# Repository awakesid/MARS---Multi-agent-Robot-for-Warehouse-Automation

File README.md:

# M.A.R.S — Multi Agent Robot System for Warehouse Automation

Modular multi-robot warehouse automation system using sensor fusion (encoders + overhead camera/ArUco) for localization, with ROS 2 based central coordination and ESP32-based robot firmware.

## Overview

- Differential-drive robots with ESP32 microcontrollers, encoder-based odometry, and servo grippers
- Overhead camera + ArUco markers for global pose estimation of robots, loads, and dropzones
- ROS 2 central controller handles task allocation, path planning, collision avoidance
- Robot ↔ central controller communication over UDP (JSON commands)
- Supports single/multi-robot operation, priority-based and thread-based task execution, single/double dropzone configurations

## System Architecture

```
Overhead Camera → aruco_detector (OpenCV) → /bot_poses, /loads, /dropzone
                                                      ↓
                                              task_manager (ROS 2)
                                        (task allocation, collision avoidance, navigation)
                                                      ↓
                                          UDP (JSON) ↔ ESP32 robots
```

## Hardware

- ESP32-WROOM / ESP32-S3
- N20 DC motors with encoders
- L293D dual H-bridge motor driver
- Servo gripper
- Li-Po battery
- Custom double-sided PCB (KiCad design, in-house etched)
- 3D printed chassis (Fusion 360 + Bambu Lab printer)

## Software Stack

- **Firmware**: C++ (Arduino/ESP32), non-blocking UDP + Telnet handlers, PID for straight-line motion
- **Central Controller**: ROS 2 (Python/C++), OpenCV for ArUco detection
- **Communication**: ROS 2 topics (internal), UDP/WiFi (robot control)

## Repository Structure

```
/firmware        # ESP32 robot firmware (motor control, encoder PID, UDP command handling)
/ros2_ws          # ROS 2 packages: camera_node, aruco_detector, task_manager
/pcb              # KiCad PCB design files
/cad              # Fusion 360 chassis design files
/docs             # Report, diagrams, results
```

## Firmware Command Protocol

Robots listen on a dedicated UDP port for JSON commands:

```json
{"id": 1, "cmd": "FORWARD", "dist": 200}
{"id": 1, "cmd": "TURN_L", "angle": 90}
{"id": 1, "cmd": "GRAB"}
```

Supported commands: `FORWARD`, `BACKWARD`, `TURN_L`, `TURN_R`, `GRAB`, `RELEASE`, `STOP`
Each command receives an `ack` on receipt and a `done` reply on completion. Odometry is broadcast at 10 Hz.

## Setup

### Firmware
1. Open `/firmware` in Arduino IDE / PlatformIO
2. Set `BOT_ID`, WiFi credentials, and target UDP port per robot
3. Flash to ESP32

### Central Controller
1. Requires ROS 2 (tested on Humble/Iron), OpenCV, `opencv-contrib` (ArUco module)
2. Build workspace:
   ```
   cd ros2_ws
   colcon build
   source install/setup.bash
   ```
3. Launch nodes:
   ```
   ros2 launch mars_bringup mars.launch.py
   ```

Thread-based multi-robot execution with double dropzone gave the best throughput; single dropzone increases collision risk and coordination overhead.

## Team
- Amrit Kumar Banjade
- Laxmi Prasad Upadhyaya
- Siddartha Gupta
- Sumit Sigdel

Department of Electronics and Computer Engineering, Pashchimanchal Campus, IOE, Tribhuvan University
Supervisor: Asst. Prof. Er. Hom Nath Tiwari

For a more detailed description, you can refer `MARS_report.pdf`

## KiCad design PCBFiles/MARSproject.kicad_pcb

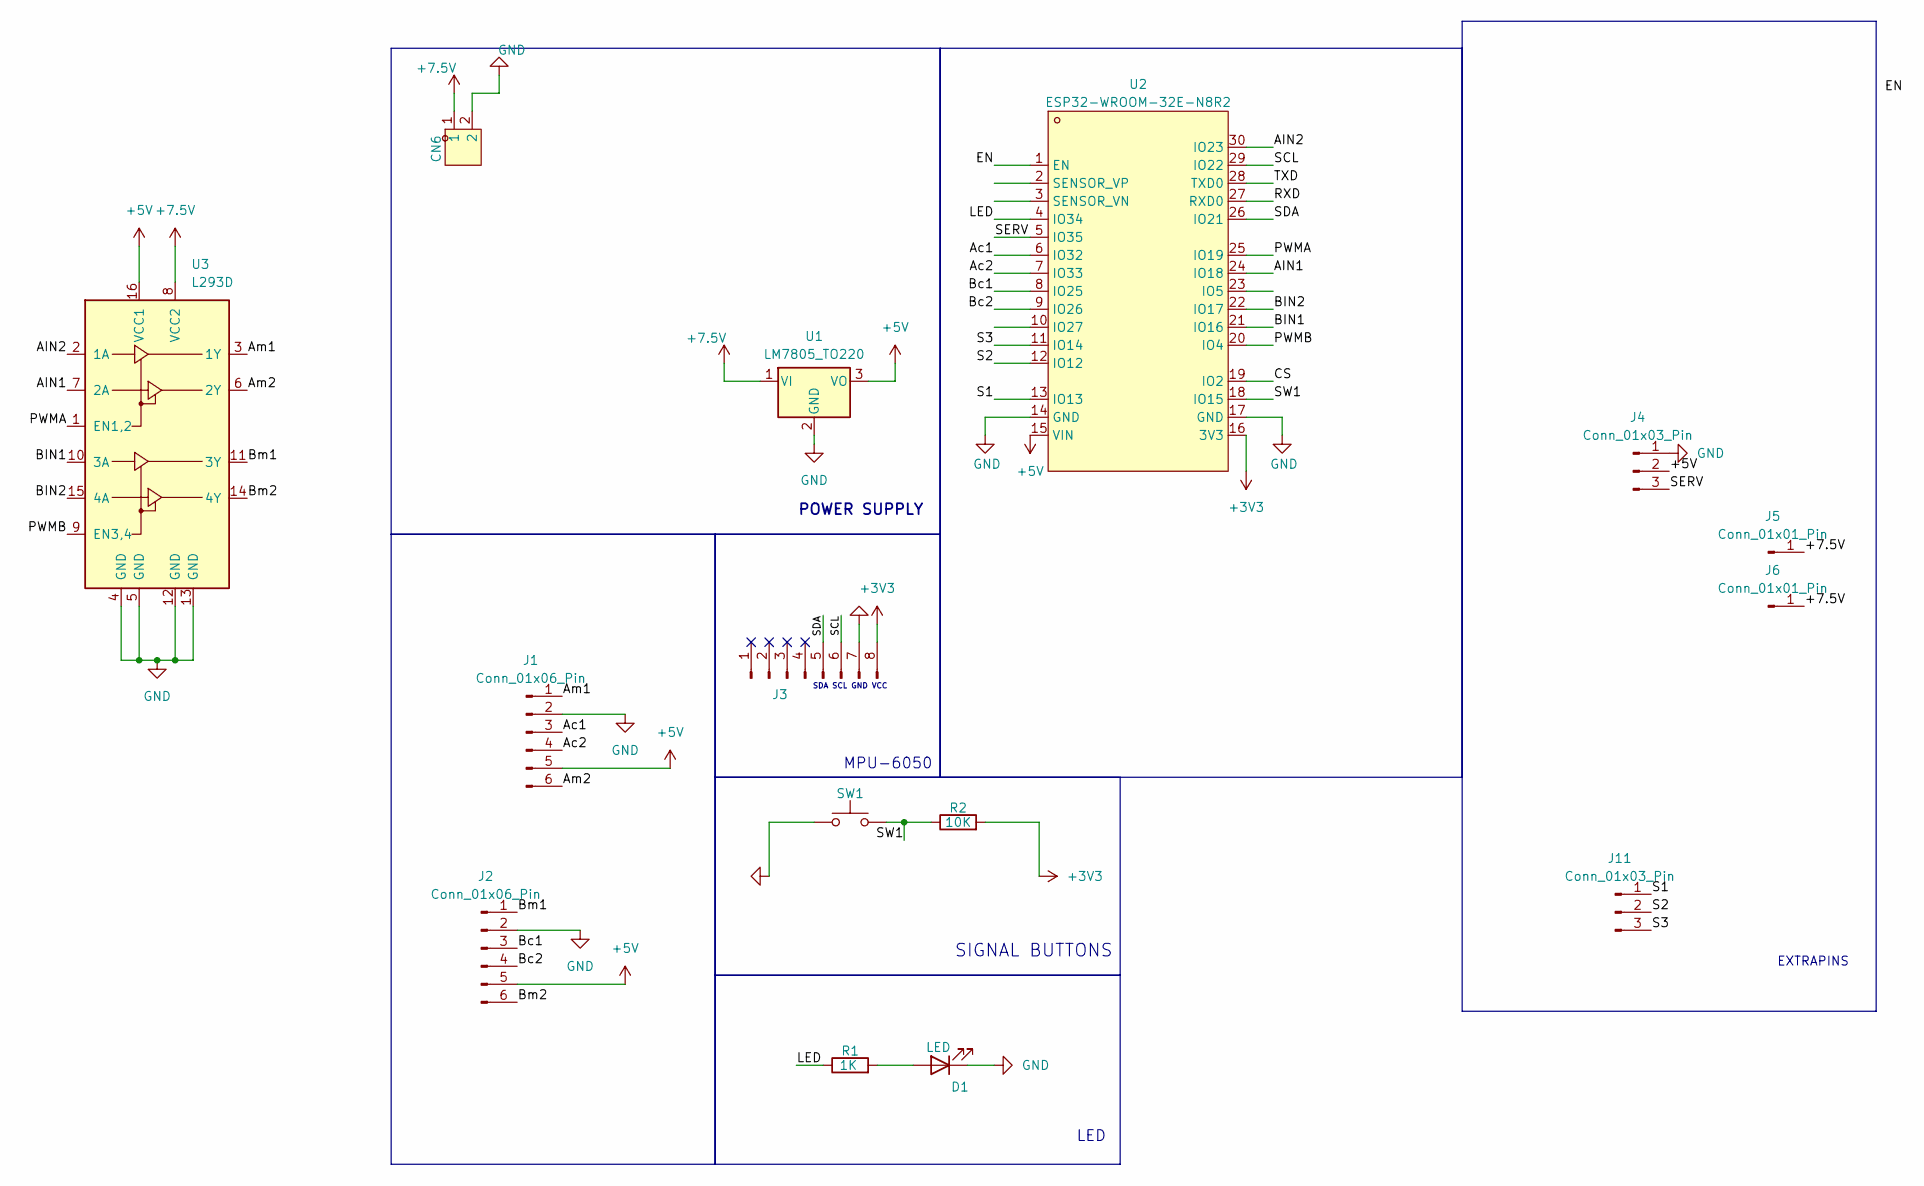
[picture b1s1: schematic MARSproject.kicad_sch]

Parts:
CN6: B2B-XH-A (LF)(SN); CONN-TH_B2B-XH-A-LF-SN; LCSC Part C158012
D1: LED; LED_D1.8mm_W3.3mm_H2.4mm
J1, J2: Conn_01x06_Pin; PinHeader_1x06_P2.54mm_Vertical
J3: Conn_01x08_Pin; PinHeader_1x08_P2.54mm_Vertical
J4, J11: Conn_01x03_Pin; PinHeader_1x03_P2.54mm_Vertical
J5, J6: Conn_01x01_Pin; PinHeader_1x01_P2.54mm_Vertical
R1: 1K; R_Axial_DIN0204_L3.6mm_D1.6mm_P2.54mm_Vertical
R2: 10K; R_Axial_DIN0204_L3.6mm_D1.6mm_P2.54mm_Vertical
SW1: SW_Push; SW_PUSH_6mm_H4.3mm
U1: LM7805_TO220; TO-220-3_Vertical
U2: ESP32-WROOM-32E-N8R2; esp32 dev board; LCSC Part C5361945
U3: L293D; DIP-16_W7.62mm

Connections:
+3V3: J3.8, R2.2, U2.16 (3V3)
+5V: J1.5, J2.5, J4.2, U1.3 (VO), U2.15 (VIN), U3.16 (VCC1)
+7.5V: CN6.1, J5.1, J6.1, U1.1 (VI), U3.8 (VCC2)
/AIN1: U2.24 (IO18), U3.7 (2A)
/AIN2: U2.30 (IO23), U3.2 (1A)
/Ac1: J1.3, U2.6 (IO32)
/Ac2: J1.4, U2.7 (IO33)
/Am1: J1.1, U3.3 (1Y)
/Am2: J1.6, U3.6 (2Y)
/BIN1: U2.21 (IO16), U3.10 (3A)
/BIN2: U2.22 (IO17), U3.15 (4A)
/Bc1: J2.3, U2.8 (IO25)
/Bc2: J2.4, U2.9 (IO26)
/Bm1: J2.1, U3.11 (3Y)
/Bm2: J2.6, U3.14 (4Y)
/CS: U2.19 (IO2)
/EN: U2.1 (EN)
/LED: R1.1, U2.4 (IO34)
/PWMA: U2.25 (IO19), U3.1 (EN1,2)
/PWMB: U2.20 (IO4), U3.9 (EN3,4)
/RXD: U2.27 (RXD0)
/S1: J11.1, U2.13 (IO13)
/S2: J11.2, U2.12 (IO12)
/S3: J11.3, U2.11 (IO14)
/SCL: J3.6, U2.29 (IO22)
/SDA: J3.5, U2.26 (IO21)
/SERV: J4.3, U2.5 (IO35)
/SW1: R2.1, SW1.2, U2.18 (IO15)
/TXD: U2.28 (TXD0)
GND: CN6.2, D1.1 (K), J1.2, J2.2, J3.7, J4.1, SW1.1, U1.2 (GND), U2.14 (GND), U2.17 (GND), U3.4 (GND), U3.5 (GND), U3.12 (GND), U3.13 (GND)
unnamed: D1.2 (A), R1.2

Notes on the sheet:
SDA SCL GND VCC
SIGNAL BUTTONS
MPU-6050
POWER SUPPLY
EXTRAPINS
LED

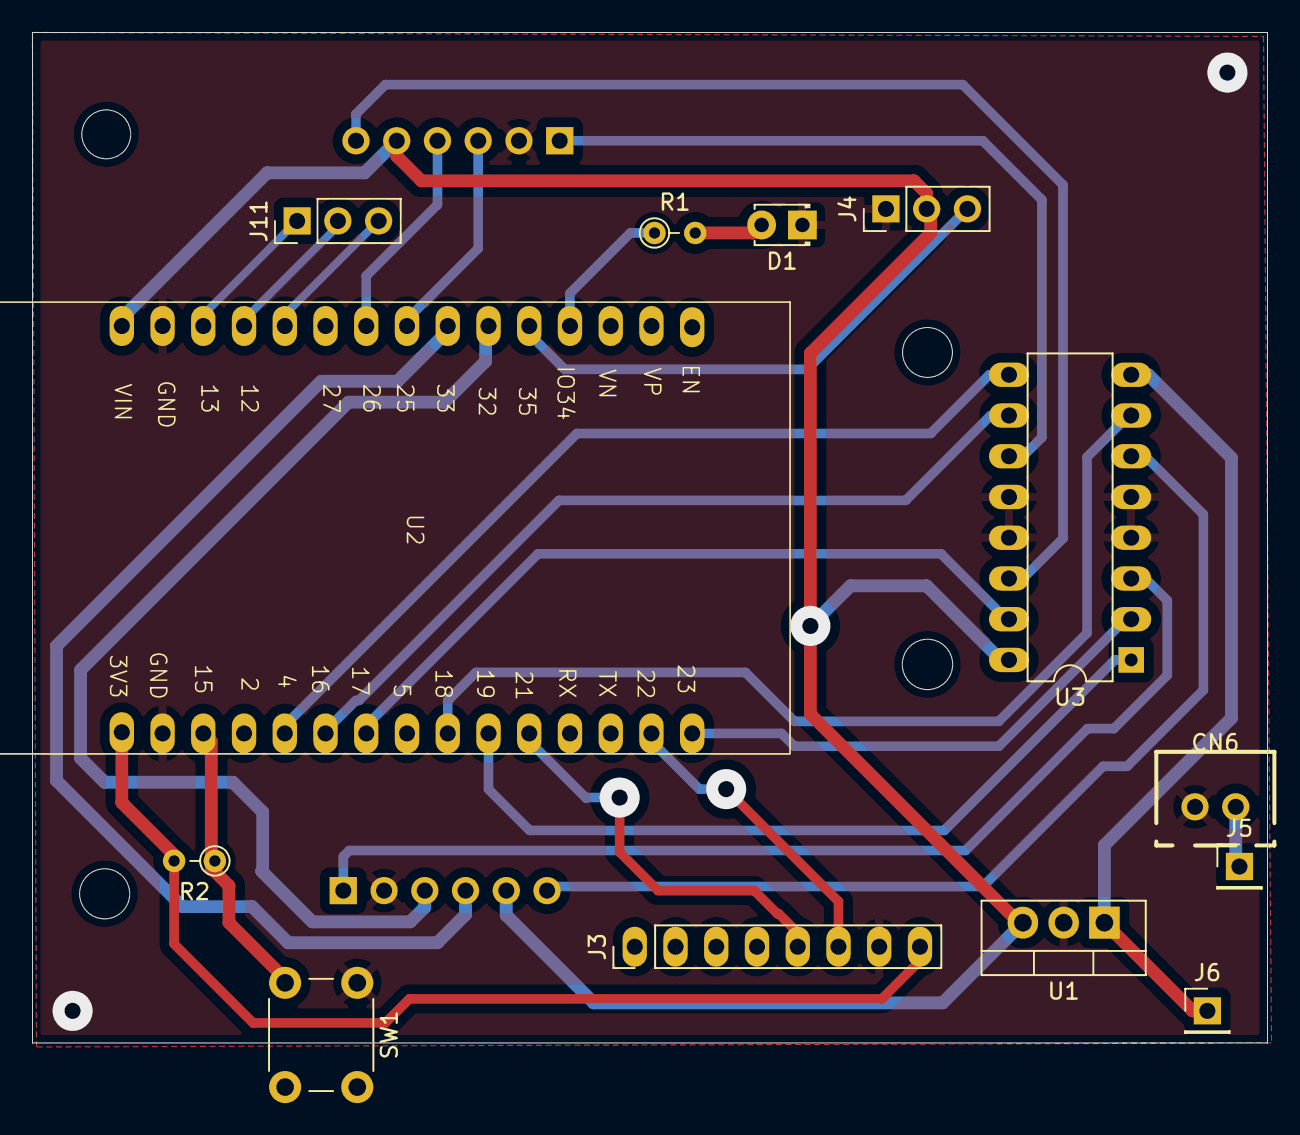
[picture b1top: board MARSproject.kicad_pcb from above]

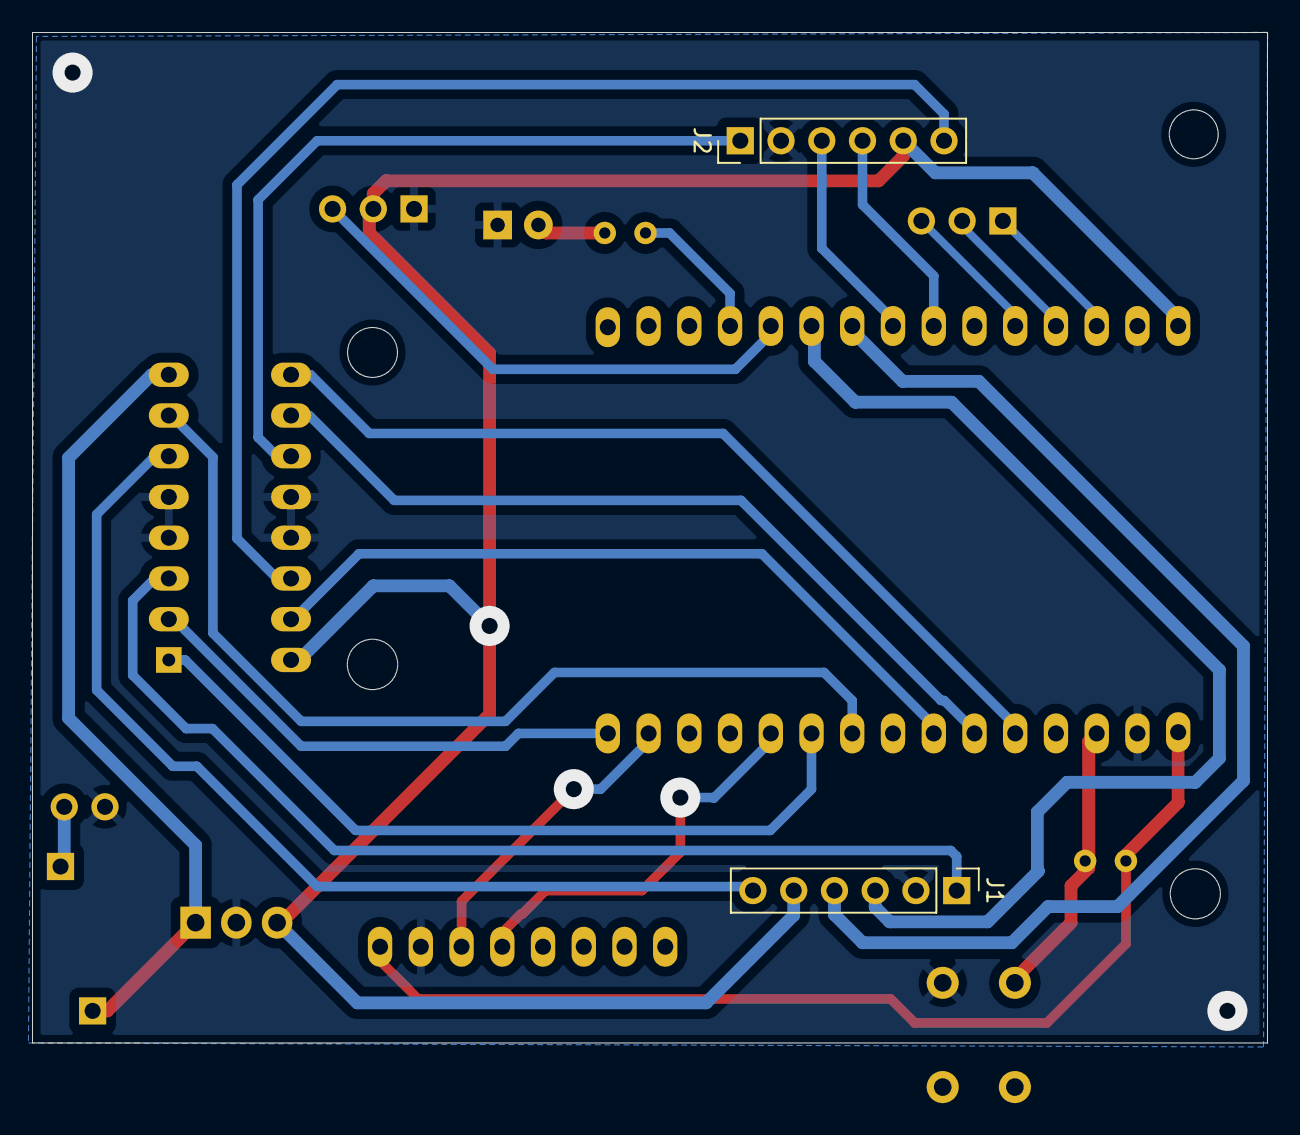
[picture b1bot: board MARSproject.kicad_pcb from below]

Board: 2 copper layers, 77.0 x 63.0 mm, 15 parts (2 on the bottom side), 27 nets.

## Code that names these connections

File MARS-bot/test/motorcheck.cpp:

#include <Arduino.h>

// Motor A
#define AIN1 18
#define AIN2 23
#define PWMA 19

// Motor B
#define BIN1 16
#define BIN2 17
#define PWMB 4

void setup()
{
    pinMode(AIN1, OUTPUT);
    pinMode(AIN2, OUTPUT);
    pinMode(PWMA, OUTPUT);

    pinMode(BIN1, OUTPUT);
    pinMode(BIN2, OUTPUT);
    pinMode(PWMB, OUTPUT);
}

// Motor A forward
void motorA_forward(int speed)
{
    digitalWrite(AIN1, HIGH);
    digitalWrite(AIN2, LOW);
    analogWrite(PWMA, speed);
}

// Motor A backward
void motorA_backward(int speed)
{
    digitalWrite(AIN1, LOW);
    digitalWrite(AIN2, HIGH);
    analogWrite(PWMA, speed);
}

// Motor A stop
void motorA_stop()
{
    digitalWrite(AIN1, LOW);
    digitalWrite(AIN2, LOW);
    analogWrite(PWMA, 0);
}

// Motor B forward
void motorB_forward(int speed)
{
    digitalWrite(BIN1, HIGH);
    digitalWrite(BIN2, LOW);
    analogWrite(PWMB, speed);
}

// Motor B backward
void motorB_backward(int speed)
{
    digitalWrite(BIN1, LOW);
    digitalWrite(BIN2, HIGH);
    analogWrite(PWMB, speed);
}

// Motor B stop
void motorB_stop()
{
    digitalWrite(BIN1, LOW);
    digitalWrite(BIN2, LOW);
    analogWrite(PWMB, 0);
}

void loop()
{
    // Forward
    motorA_forward(200);
    motorB_forward(200);
    delay(2000);

    // Stop
    motorA_stop();
    motorB_stop();
    delay(1000);

    // Backward
    motorA_backward(200);
    motorB_backward(200);
    delay(2000);

    // Stop
    motorA_stop();
    motorB_stop();
    delay(1000);
}
